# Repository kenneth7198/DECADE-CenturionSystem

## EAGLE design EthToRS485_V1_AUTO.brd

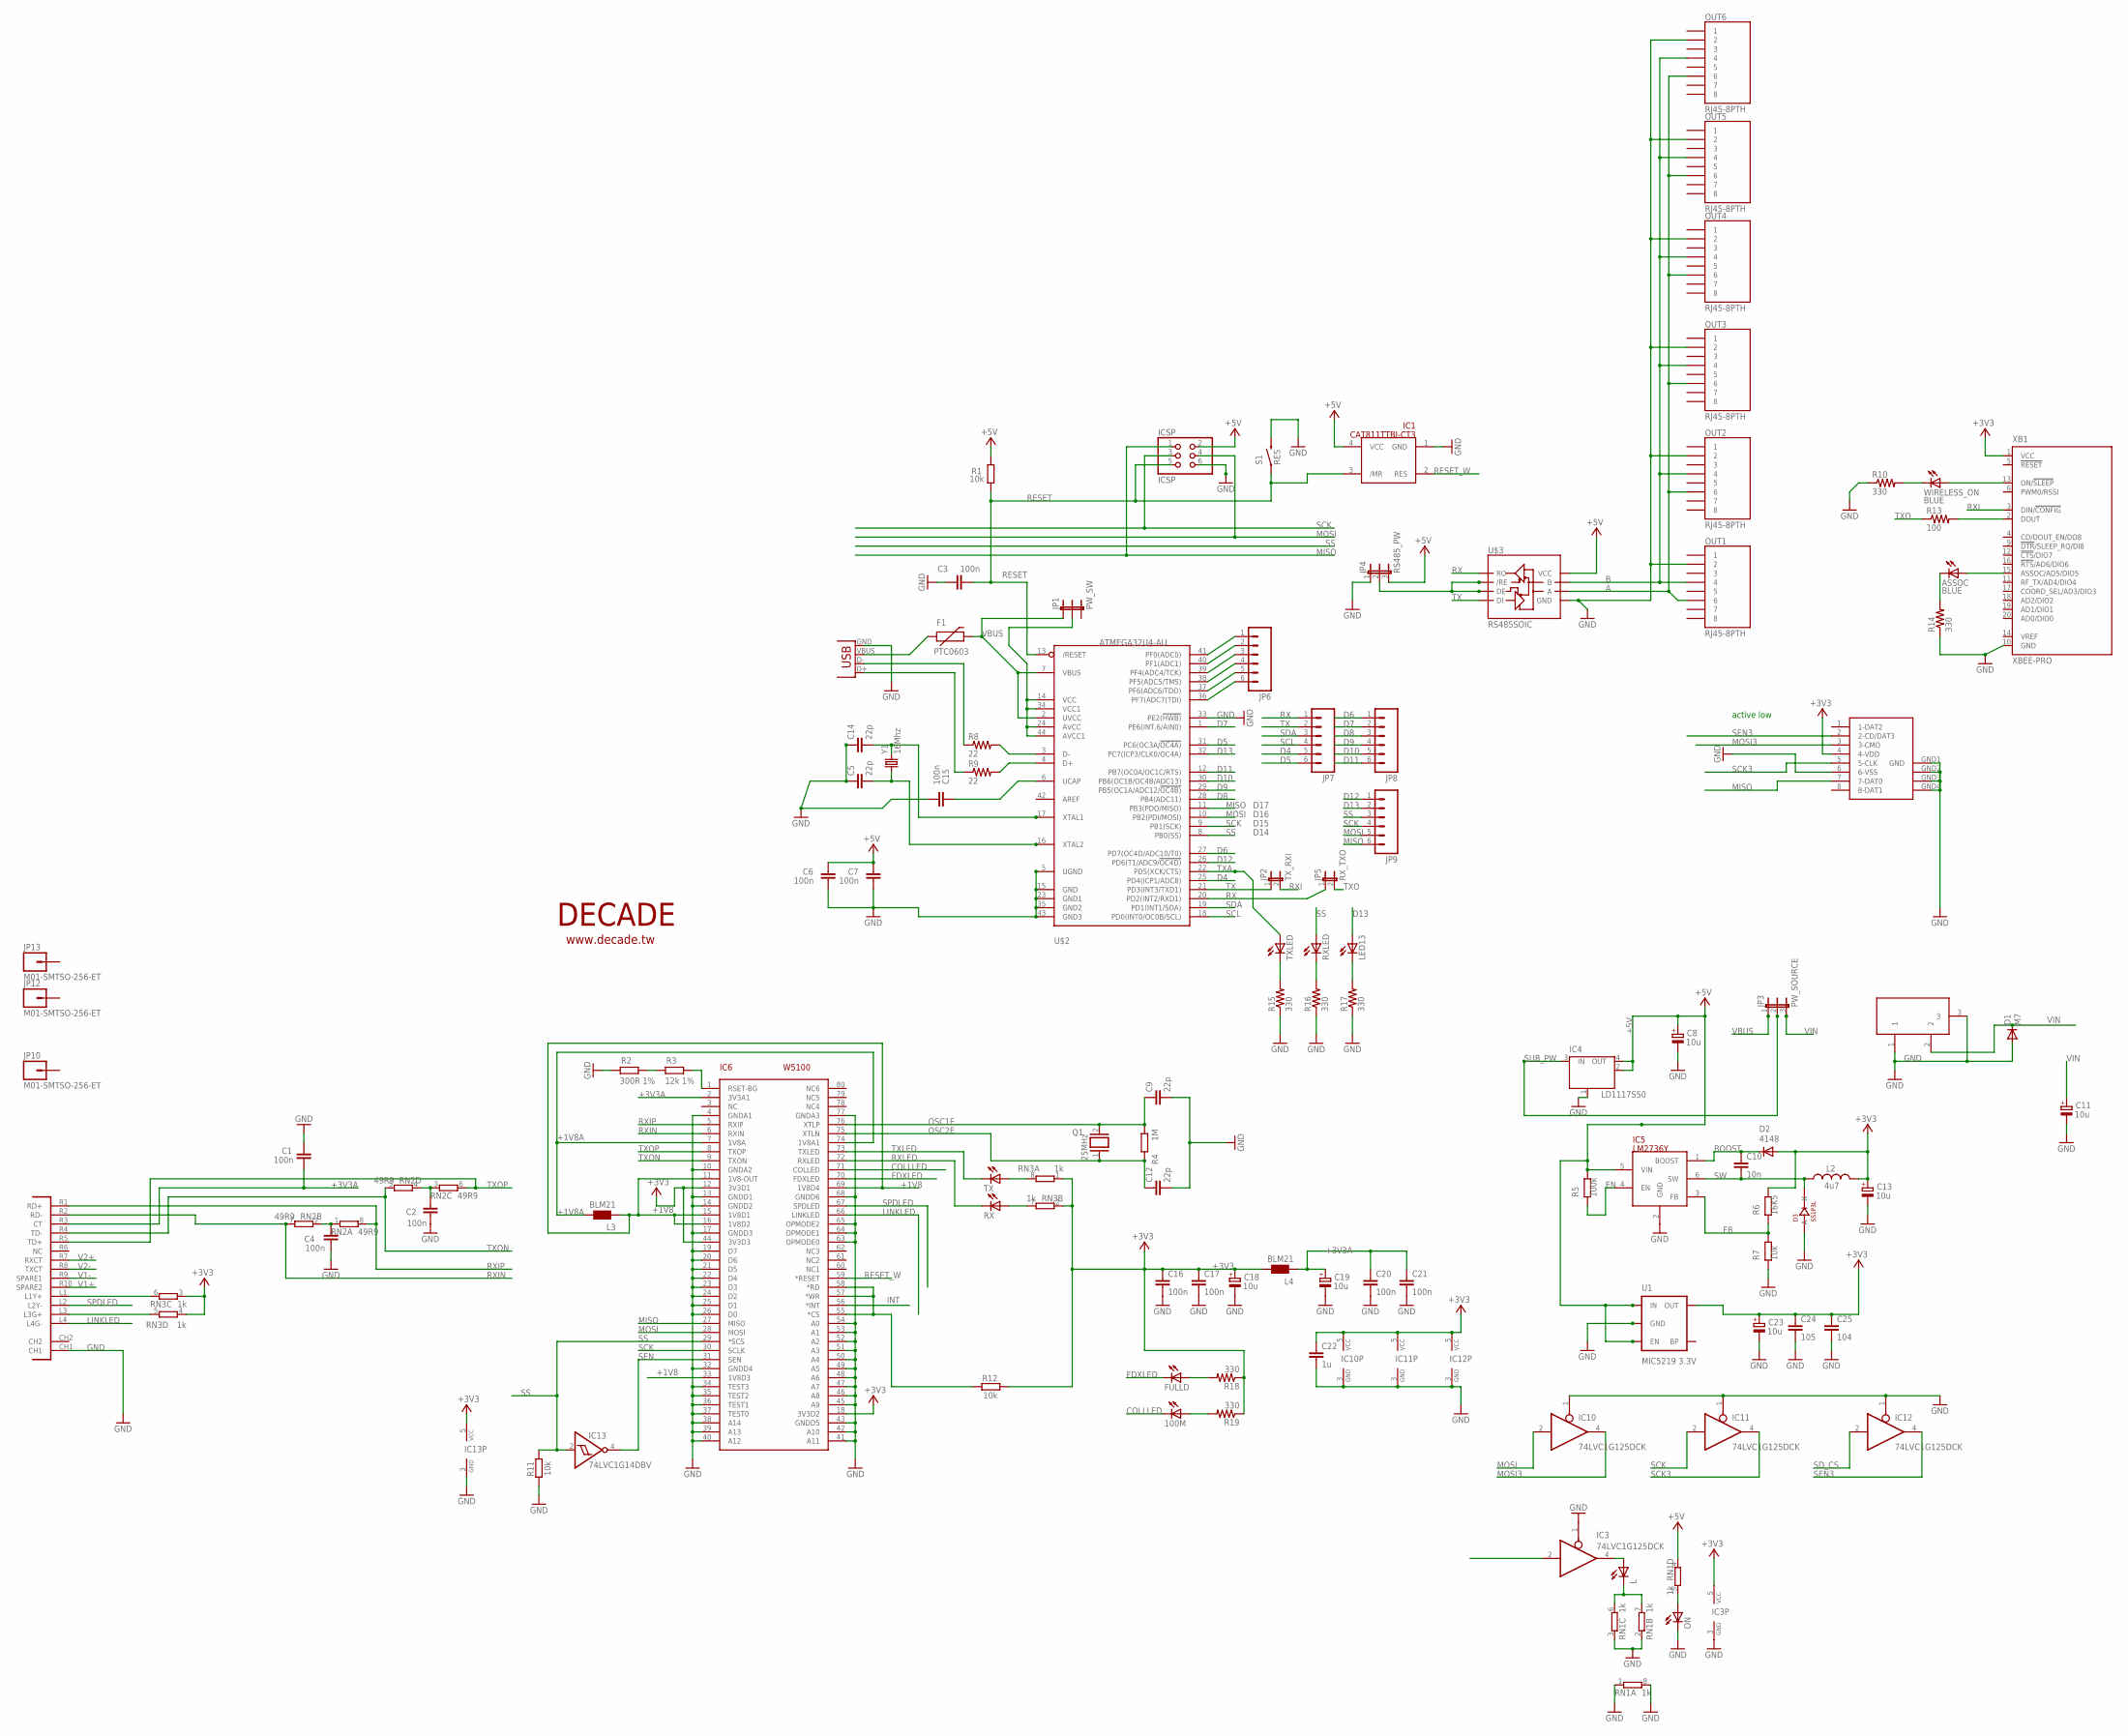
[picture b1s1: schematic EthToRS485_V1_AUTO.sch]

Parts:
100M: LEDCHIPLED_0805; CHIPLED_0805
ASSOC: BLUE; CHIPLED_0805
C1, C2, C3, C4, C6, C7, C15, C16, C17, C20, C21: 100n; C0603-ROUND
C5, C14: 22p; 0805
C8, C11, C13, C18, C19, C23: 10u; SMC_B
C9, C12: 22p; C0603-ROUND
C10: 10n; C0603-ROUND
C22: 1u; C0603-ROUND
C24: 105; C0603-ROUND
C25: 104; C0603-ROUND
D1: M7; SMB
D2: 4148; MINIMELF
D3: SS1P3L; DO220AAL
F1: PTC0603; 0603
FULLD: LEDCHIPLED_0805; CHIPLED_0805
IC1: CAT811TTBI-CT3; SOT143
IC3, IC10, IC11, IC12: 74LVC1G125DCK; SC70-5
IC4: LD1117S50; SOT223
IC5: LM2736Y; SOT23-6
IC6: W5100; SQFP-S-10X10-80
IC13: 74LVC1G14DBV; SOT23-5
ICSP: ICSP; 2X03
JP1: PW_SW; SJ_3
JP2: TX_RXI; JP1
JP3: PW_SOURCE; JP2
JP4: RS485_PW; JP2
JP5: RX_TXO; JP1
JP6, JP7, JP8, JP9: M06SIP; 1X06
JP10, JP12, JP13: M01-SMTSO-256-ET; SMTSO-256-ET
L: LEDCHIPLED_0805; CHIPLED_0805
L2: 4u7; SRR0604
L3, L4: BLM21; 0805
LED13: LEDCHIPLED_0805; CHIPLED_0805
ON: LEDCHIPLED_0805; CHIPLED_0805
OUT1, OUT2, OUT3, OUT4, OUT5, OUT6: RJ45-8PTH; RJ45-8
Q1: 25MHz; QS
R1, R7, R11, R12: 10k; R0603-ROUND
R2: 300R 1%; R0603-ROUND
R3: 12k 1%; R0603-ROUND
R4: 1M; R0603-ROUND
R5: 100k; R0603-ROUND
R6: 16K5; R0603-ROUND
R8, R9: 22; 0805
R10, R14, R15, R16, R17, R18, R19: 330; 0805
R13: 100; 0805
RN1, RN3: 1k; CAY16
RN2: 49R9; CAY16
RX: LEDCHIPLED_0805; CHIPLED_0805
RXLED: LEDCHIPLED_0805; CHIPLED_0805
S1: RES; TACTILE-SWITCH-1101NE
TX: LEDCHIPLED_0805; CHIPLED_0805
TXLED: LEDCHIPLED_0805; CHIPLED_0805
U1: MIC5219 3.3V; SOT23-5
U$1: POE-RJ45
U$2: ATMEGA32U4-AU; TQFP44
U$3: RS485SOIC; SO08
U$4: DECADE-LOGO-SMALL
WIRELESS_ON: BLUE; CHIPLED_0805
X1: DC21MMX; DC-21MM
X2: SDCARD-15TW-8821
X3: USBOLD; USB-MINIB-OLD
XB1: XBEE-PRO
Y1: 16Mhz; CRYSTAL-SMD-5X3

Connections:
+1V8: IC6.11 (1V8-OUT), IC6.15 (1V8D1), IC6.16 (1V8D2), IC6.33 (1V8D3), IC6.69 (1V8D4), L3.1
+1V8A: IC6.7 (1V8A), IC6.74 (1V8A1), L3.2
+3V3: C13.+, C16.1, C17.1, C18.+, C22.1, C23.+, C24.1, C25.1, D2.A, IC3.5 (VCC), IC6.12 (3V3D1), IC6.18 (3V3D2), IC6.44 (3V3D3), IC10.5 (VCC), IC11.5 (VCC), IC12.5 (VCC), IC13.5 (VCC), L2.P$2 (2), L4.2, R6.1, R12.2, R18.1, R19.1, RN3.1, RN3.2 (1), RN3.3 (1), RN3.4 (1), U1.5 (OUT), X2.4 (4-VDD), XB1.1 (VCC)
+3V3A: C1.1, C19.+, C20.1, C21.1, IC6.2 (3V3A1), L4.1, U$1.R3 (CT)
+5V: C6.1, C7.1, C8.+, IC1.4 (VCC), IC4.2 (OUT), IC4.4 (OUT), IC5.5 (VIN), ICSP.2, JP4.3, R1.2, R5.1, RN1.4 (1), U1.1 (IN), U1.3 (EN), U$3.8 (VCC)
A: OUT1.6, OUT2.6, OUT3.6, OUT4.6, OUT5.6, OUT6.6, U$3.6 (A)
AD0: JP6.1, U$2.41 (PF0(ADC0))
AD1: JP6.2, U$2.40 (PF1(ADC1))
AD2: JP6.3, U$2.39 (PF4(ADC4/TCK))
AD3: JP6.4, U$2.38 (PF5(ADC5/TMS))
AD4: JP6.5, U$2.37 (PF6(ADC6/TDO))
AD5: JP6.6, U$2.36 (PF7(ADC7(TDI))
B: OUT1.4, OUT2.4, OUT3.4, OUT4.4, OUT5.4, OUT6.4, U$3.7 (B)
BOOST: C10.1, D2.C, IC5.1 (BOOST)
COLLLED: 100M.C, IC6.71 (COLLED)
D4: JP7.5, U$2.25 (PD4(ICP1/ADC8))
D5: JP7.6, U$2.31 (PC6(OC3A/!OC4A))
D6: JP8.1, U$2.27 (PD7(OC4D/ADC10/T0))
D7: JP8.2, U$2.1 (PE6(INT.6/AIN0))
D8: JP8.3, U$2.28 (PB4(ADC11))
D9: JP8.4, U$2.29 (PB5(OC1A/ADC12/!OC4B))
D10: JP8.5, U$2.30 (PB6(OC1B/OC4B/ADC13))
D11: JP8.6, U$2.12 (PB7(OC0A/OC1C/RTS))
D12: JP9.1, U$2.26 (PD6(T1/ADC9/!OC4D))
D13: JP9.2, LED13.A, U$2.32 (PC7(ICP3/CLK0/OC4A))
EN: IC5.4 (EN), R5.2
FB: IC5.3 (FB), R6.2, R7.1
FDXLED: FULLD.C, IC6.70 (FDXLED)
GND: C1.2, C2.1, C3.2, C4.1, C5.1, C6.2, C7.2, C8.-, C9.2, C11.-, C12.2, C13.-, C14.1, C15.2, C16.2, C17.2, C18.-, C19.-, C20.2, C21.2, C22.2, C23.-, C24.2, C25.2, D1.A, D3.P$2 (A), IC1.1 (GND), IC3.1 (OE), IC3.3 (GND), IC4.1 (GND/ADJ), IC5.2 (GND), IC6.4 (GNDA1), IC6.10 (GNDA2), IC6.13 (GNDD1), IC6.14 (GNDD2), IC6.17 (GNDD3), IC6.19 (D7), IC6.20 (D6), IC6.21 (D5), IC6.22 (D4), IC6.23 (D3), IC6.24 (D2), IC6.25 (D1), IC6.26 (D0), IC6.32 (GNDD4), IC6.34 (TEST3), IC6.35 (TEST2), IC6.36 (TEST1), IC6.37 (TEST0), IC6.38 (A14), IC6.39 (A13), IC6.40 (A12), IC6.41 (A11), IC6.42 (A10), IC6.43 (GNDD5), IC6.45 (A9), IC6.46 (A8), IC6.47 (A7), IC6.48 (A6), IC6.49 (A5), IC6.50 (A4), IC6.51 (A3), IC6.52 (A2), IC6.53 (A1), IC6.54 (A0), IC6.63 (OPMODE0), IC6.64 (OPMODE1), IC6.65 (OPMODE2), IC6.68 (GNDD6), IC6.77 (GNDA3), IC10.1 (OE), IC10.3 (GND), IC11.1 (OE), IC11.3 (GND), IC12.1 (OE), IC12.3 (GND), IC13.3 (GND), ICSP.6, JP4.1, ON.C, OUT1.2, OUT2.2, OUT3.2, OUT4.2, OUT5.2, OUT6.2, R2.2, R7.2, R10.1, R11.1, R14.1, R15.1, R16.1, R17.1, RN1.1, RN1.2 (1), RN1.3 (1), RN1.8 (2), S1.P$2 (2), U1.2 (GND), U$1.CH1, U$2.5 (UGND), U$2.15 (GND), U$2.23 (GND1), U$2.33 (PE2(!HWB)), U$2.35 (GND2), U$2.43 (GND3), U$3.5 (GND), X1.1, X1.3, X2.6 (6-VSS), X2.GND1 (GND), X2.GND2 (GND1), X2.GND3 (GND2), X2.GND4 (GND3), X3.GND, XB1.10 (GND)
INT: IC6.56 (*INT)
LINKLED: IC6.66 (LINKLED), U$1.L4 (L4G-)
MISO: IC6.27 (MISO), ICSP.1, JP9.6, U$2.11 (PB3(PDO/MISO)), X2.7 (7-DAT0)
MOSI: IC6.28 (MOSI), IC10.2 (I), ICSP.4, JP9.5, U$2.10 (PB2(PDI/MOSI))
MOSI3: IC10.4 (O), X2.3 (3-CMO)
unnamed: IC3.4 (O), L.A
unnamed: RN3.5 (2), U$1.L3 (L3G+)
unnamed: RN3.6 (2), U$1.L1 (L1Y+)
unnamed: L.C, RN1.6 (2), RN1.7 (2)
unnamed: C5.2, U$2.16 (XTAL2), Y1.1
unnamed: C14.2, U$2.17 (XTAL1), Y1.3 (2)
unnamed: ON.A, RN1.5 (2)
unnamed: RN3.8 (2), TX.A
unnamed: C2.2, RN2.3 (1), RN2.4 (1)
unnamed: R8.2, U$2.3 (D-)
unnamed: R9.2, U$2.4 (D+)
unnamed: R8.1, X3.D-
unnamed: R9.1, X3.D+
unnamed: F1.1, X3.VBUS
unnamed: R15.2, TXLED.C
unnamed: R13.2, XB1.2 (DOUT)
unnamed: C15.1, U$2.6 (UCAP)
unnamed: JP1.2, U$2.14 (VCC), U$2.24 (AVCC), U$2.34 (VCC1), U$2.44 (AVCC1)
unnamed: R10.2, WIRELESS_ON.C
unnamed: JP4.2, U$3.2 (/RE), U$3.3 (DE)
unnamed: RN3.7 (2), RX.A
unnamed: WIRELESS_ON.A, XB1.13 (ON/!SLEEP)
unnamed: ASSOC.A, XB1.15 (ASSOC/AD5/DIO5)
unnamed: ASSOC.C, R14.2
unnamed: FULLD.A, R18.2
unnamed: C4.2, RN2.1, RN2.2 (1)
unnamed: R2.1, R3.2
unnamed: IC6.1 (RSET-BG), R3.1
unnamed: IC6.55 (*CS), IC6.57 (*WR), IC6.58 (*RD), R12.1
unnamed: R16.2, RXLED.C
unnamed: LED13.C, R17.2
unnamed: 100M.A, R19.2
OSC1E: C9.1, IC6.76 (XTLP), Q1.2, R4.1
OSC2E: C12.1, IC6.75 (XTLN), Q1.1, R4.2
RESET: C3.1, IC1.3 (/MR), ICSP.5, R1.1, S1.P$1 (1), U$2.13 (/RESET)
RESET_W: IC1.2 (RES), IC6.59 (*RESET)
RX: JP5.1, JP7.1, U$2.20 (PD2(INT2/RXD1)), U$3.1 (RO)
RXI: JP2.2, XB1.3 (DIN/!CONFIG)
RXIN: IC6.6 (RXIN), RN2.7 (2), U$1.R2 (RD-)
RXIP: IC6.5 (RXIP), RN2.8 (2), U$1.R1 (RD+)
RXLED: IC6.72 (RXLED), RX.C
SCK: IC6.30 (SCLK), IC11.2 (I), ICSP.3, JP9.4, U$2.9 (PB1(SCK))
SCK3: IC11.4 (O), X2.5 (5-CLK)
SCL: JP7.4, U$2.18 (PD0(INT0/OC0B/SCL))
SDA: JP7.3, U$2.19 (PD1(INT1/SDA))
SD_CS: IC12.2 (I)
SEN: IC6.31 (SEN), IC13.4 (O)
SEN3: IC12.4 (O), X2.2 (2-CD/DAT3)
SPDLED: IC6.67 (SPDLED), U$1.L2 (L2Y-)
SS: IC6.29 (*SCS), IC13.2 (I), JP9.3, R11.2, RXLED.A, U$2.8 (PB0(SS))
SUB_PW: IC4.3 (IN), JP3.2
SW: C10.2, D3.P$1 (K), IC5.6 (SW), L2.P$1 (1)
TX: JP2.1, JP7.2, U$2.21 (PD3(INT3/TXD1)), U$3.4 (DI)
TXA: TXLED.A, U$2.22 (PD5(XCK/CTS))
TXLED: IC6.73 (TXLED), TX.C
TXO: JP5.2, R13.1
TXON: IC6.9 (TXON), RN2.5 (2), U$1.R4 (TD-)
TXOP: IC6.8 (TXOP), RN2.6 (2), U$1.R5 (TD+)
V1+: U$1.R10 (SPARE2)
V1-: U$1.R9 (SPARE1)
V2+: U$1.R7 (RXCT)
V2-: U$1.R8 (TXCT)
VBUS: F1.2, JP1.1, JP3.1, U$2.2 (UVCC), U$2.7 (VBUS)
VIN: C11.+, D1.C, JP3.3, X1.2

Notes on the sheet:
active low
D15
D14
D16
D17

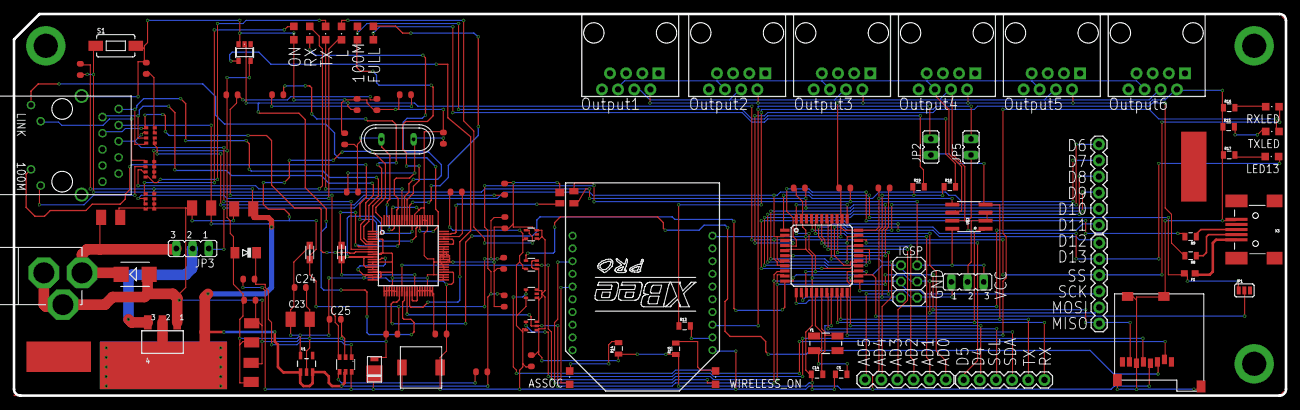
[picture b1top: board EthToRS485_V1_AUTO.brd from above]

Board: 2 copper layers, 200.0 x 60.0 mm, 105 parts (0 on the bottom side), 92 nets.

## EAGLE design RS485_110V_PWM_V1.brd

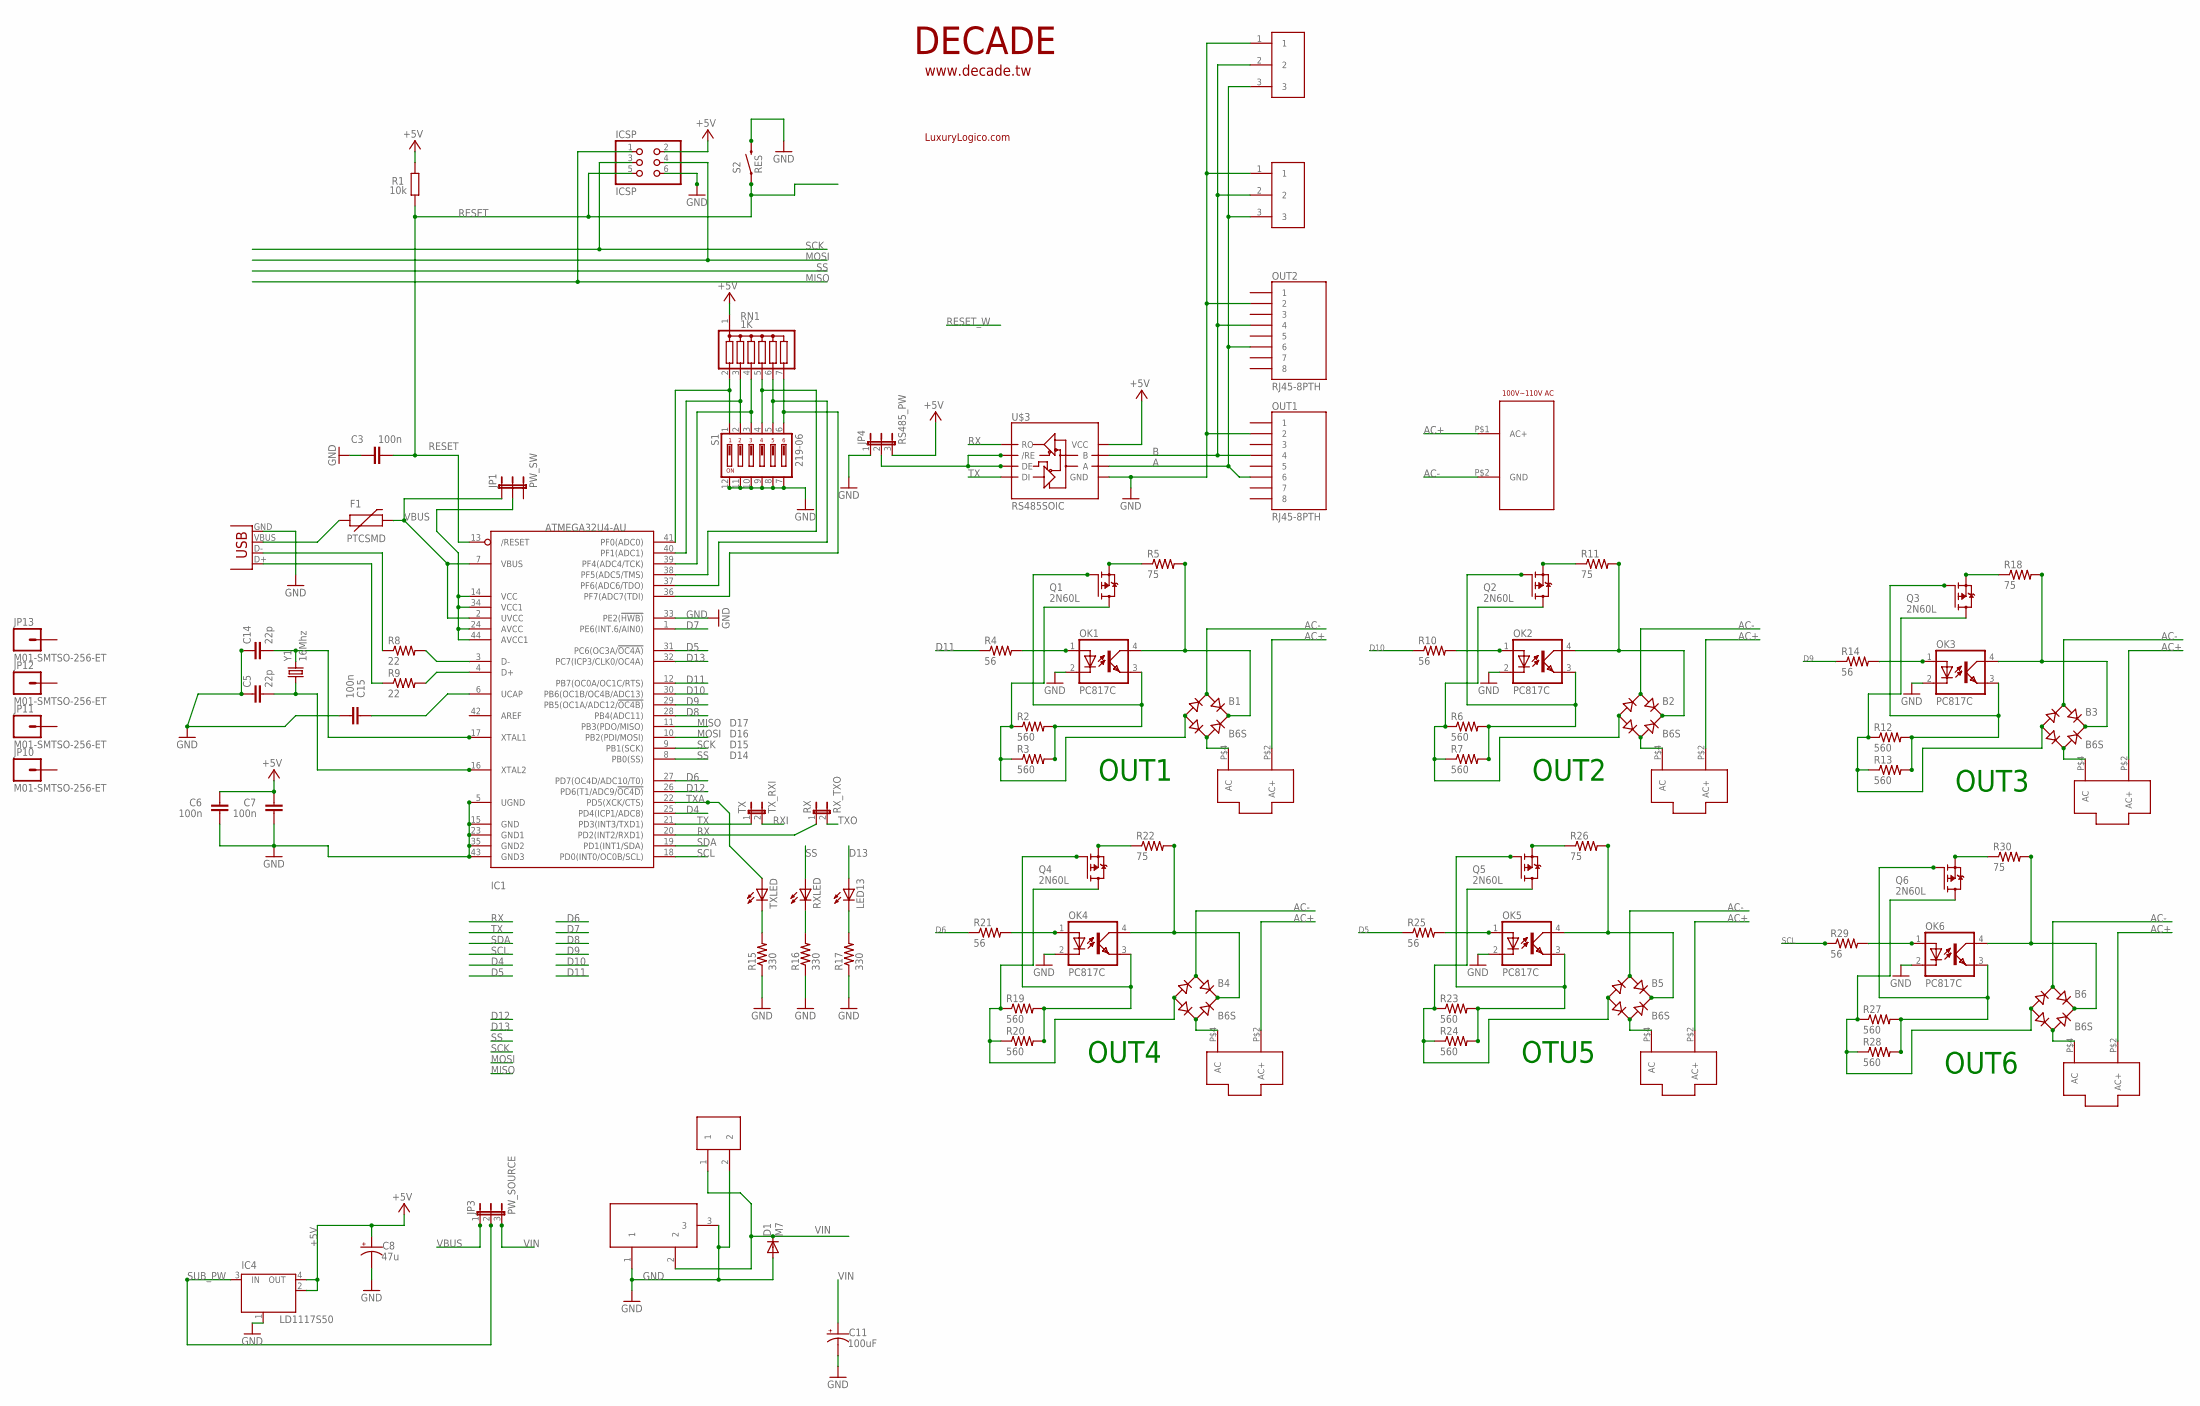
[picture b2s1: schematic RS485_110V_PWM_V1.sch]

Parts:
B1, B2, B3, B4, B5, B6: B6S; MBS
C3, C6, C7, C15: 100n; C0603-ROUND
C5, C14: 22p; 0805
C8: 47u; PANASONIC_E
C11: 100uF; PANASONIC_E
D1: M7; SMB
F1: PTCSMD; PTC-1206
IC1: ATMEGA32U4-AU; TQFP44
IC4: LD1117S50; SOT223
ICSP: ICSP; 2X03
JP1: PW_SW; SJ_3
JP3: PW_SOURCE; JP2
JP4: RS485_PW; JP2
JP10, JP11, JP12, JP13: M01-SMTSO-256-ET; SMTSO-256-ET
LED13: LEDCHIPLED_0805; CHIPLED_0805
OK1, OK2, OK3, OK4, OK5, OK6: PC817C; DIP4-400
OUT1, OUT2: RJ45-8PTH; RJ45-8
Q1, Q2, Q3, Q4, Q5, Q6: 2N60L; TO252
R1: 10k; R0603-ROUND
R2, R3, R6, R7, R12, R13, R19, R20, R23, R24, R27, R28: 560; 1206
R4, R10, R14, R21, R25, R29: 56; 1206
R5, R11, R18, R22, R26, R30: 75; AXIAL-0.6
R8, R9: 22; 0805
R15, R16, R17: 330; 0805
RN1: 1K; SIL7
RX: RX_TXO; JP1
RXLED: LEDCHIPLED_0805; CHIPLED_0805
S1: 219-06; CTS-219-06
S2: RES; TACTILE-SWITCH-1101NE
TX: TX_RXI; JP1
TXLED: LEDCHIPLED_0805; CHIPLED_0805
U$1: DECADE-ACIN; DECADE-AC_IN
U$2, U$4, U$5, U$6, U$7, U$8: DECADE-ACPW; DECADE-ACPWR
U$3: RS485SOIC; SO08
U$9: DECADE-5MM-CONN; DECADE-5MM-CON-1X2
U$10, U$11: DECADE-5MM-CON-1X3
U$12: DECADE-LOGO-SMALL
U$13: LL-LUXURYLOGICO.COM; DECADE-LL-LOGO-SMALL
X1: DC21MMX; DC-21MM
X3: USBOLD; USB-MINIB-OLD
Y1: 16Mhz; CRYSTAL-SMD-5X3

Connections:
+5V: C6.1, C7.1, C8.+, IC4.2 (OUT), IC4.4 (OUT), ICSP.2, JP4.3, R1.2, RN1.1, U$3.8 (VCC)
A: OUT1.6, OUT2.6, U$3.6 (A), U$10.3, U$11.3
AC+: U$1.P$1 (AC+), U$2.P$2 (AC+), U$4.P$2 (AC+), U$5.P$2 (AC+), U$6.P$2 (AC+), U$7.P$2 (AC+), U$8.P$2 (AC+)
AC-: B1.AC1, B2.AC1, B3.AC1, B4.AC1, B5.AC1, B6.AC1, U$1.P$2 (GND)
B: OUT1.4, OUT2.4, U$3.7 (B), U$10.2, U$11.2
D4: IC1.25 (PD4(ICP1/ADC8))
D5: IC1.31 (PC6(OC3A/!OC4A)), R25.1
D6: IC1.27 (PD7(OC4D/ADC10/T0)), R21.1
D7: IC1.1 (PE6(INT.6/AIN0))
D8: IC1.28 (PB4(ADC11))
D9: IC1.29 (PB5(OC1A/ADC12/!OC4B)), R14.1
D10: IC1.30 (PB6(OC1B/OC4B/ADC13)), R10.1
D11: IC1.12 (PB7(OC0A/OC1C/RTS)), R4.1
D12: IC1.26 (PD6(T1/ADC9/!OC4D))
D13: IC1.32 (PC7(ICP3/CLK0/OC4A)), LED13.A
GND: C3.2, C5.1, C6.2, C7.2, C8.-, C11.-, C14.1, C15.2, D1.A, IC1.5 (UGND), IC1.15 (GND), IC1.23 (GND1), IC1.33 (PE2(!HWB)), IC1.35 (GND2), IC1.43 (GND3), IC4.1 (GND/ADJ), ICSP.6, JP4.1, OK1.2 (C), OK2.2 (C), OK3.2 (C), OK4.2 (C), OK5.2 (C), OK6.2 (C), OUT1.2, OUT2.2, R15.1, R16.1, R17.1, S1.7, S1.8, S1.9, S1.10, S1.11, S1.12, S2.P$2 (2), U$3.5 (GND), U$9.2, U$10.1, U$11.1, X1.1, X1.3, X3.GND
MISO: IC1.11 (PB3(PDO/MISO)), ICSP.1
MOSI: IC1.10 (PB2(PDI/MOSI)), ICSP.4
unnamed: OK1.1 (A), R4.2
unnamed: Q1.2 (S), R5.P$1 (1)
unnamed: OK1.3 (EMIT), Q1.1 (G), R2.2, R3.2
unnamed: OK2.1 (A), R10.2
unnamed: Q2.2 (S), R11.P$1 (1)
unnamed: C5.2, IC1.16 (XTAL2), Y1.1
unnamed: C14.2, IC1.17 (XTAL1), Y1.3 (2)
unnamed: B1.-, Q1.3 (D), R2.1, R3.1
unnamed: OK2.3 (EMIT), Q2.1 (G), R6.2, R7.2
unnamed: B1.AC2, U$2.P$4 (AC)
unnamed: IC1.3 (D-), R8.2
unnamed: IC1.4 (D+), R9.2
unnamed: R8.1, X3.D-
unnamed: R9.1, X3.D+
unnamed: F1.1, X3.VBUS
unnamed: R15.2, TXLED.C
unnamed: B2.-, Q2.3 (D), R6.1, R7.1
unnamed: C15.1, IC1.6 (UCAP)
unnamed: IC1.14 (VCC), IC1.24 (AVCC), IC1.34 (VCC1), IC1.44 (AVCC1), JP1.2
unnamed: B1.+, OK1.4 (COL), R5.P$2 (2)
unnamed: JP4.2, U$3.2 (/RE), U$3.3 (DE)
unnamed: B2.AC2, U$4.P$4 (AC)
unnamed: B2.+, OK2.4 (COL), R11.P$2 (2)
unnamed: OK3.1 (A), R14.2
unnamed: Q3.2 (S), R18.P$1 (1)
unnamed: OK3.3 (EMIT), Q3.1 (G), R12.2, R13.2
unnamed: B3.-, Q3.3 (D), R12.1, R13.1
unnamed: B3.AC2, U$5.P$4 (AC)
unnamed: B3.+, OK3.4 (COL), R18.P$2 (2)
unnamed: OK4.1 (A), R21.2
unnamed: Q4.2 (S), R22.P$1 (1)
unnamed: OK4.3 (EMIT), Q4.1 (G), R19.2, R20.2
unnamed: B4.-, Q4.3 (D), R19.1, R20.1
unnamed: B4.AC2, U$6.P$4 (AC)
unnamed: B4.+, OK4.4 (COL), R22.P$2 (2)
unnamed: OK5.1 (A), R25.2
unnamed: R16.2, RXLED.C
unnamed: LED13.C, R17.2
unnamed: Q5.2 (S), R26.P$1 (1)
unnamed: IC1.41 (PF0(ADC0)), RN1.2, S1.1
unnamed: IC1.40 (PF1(ADC1)), RN1.3, S1.2
unnamed: IC1.39 (PF4(ADC4/TCK)), RN1.4, S1.3
unnamed: IC1.38 (PF5(ADC5/TMS)), RN1.5, S1.4
unnamed: IC1.37 (PF6(ADC6/TDO)), RN1.6, S1.5
unnamed: IC1.36 (PF7(ADC7(TDI)), RN1.7, S1.6
unnamed: OK5.3 (EMIT), Q5.1 (G), R23.2, R24.2
unnamed: B5.-, Q5.3 (D), R23.1, R24.1
unnamed: B5.AC2, U$7.P$4 (AC)
unnamed: B5.+, OK5.4 (COL), R26.P$2 (2)
unnamed: OK6.1 (A), R29.2
unnamed: Q6.2 (S), R30.P$1 (1)
unnamed: OK6.3 (EMIT), Q6.1 (G), R27.2, R28.2
unnamed: B6.-, Q6.3 (D), R27.1, R28.1
unnamed: B6.AC2, U$8.P$4 (AC)
unnamed: B6.+, OK6.4 (COL), R30.P$2 (2)
RESET: C3.1, IC1.13 (/RESET), ICSP.5, R1.1, S2.P$1 (1)
RX: IC1.20 (PD2(INT2/RXD1)), RX.1, U$3.1 (RO)
RXI: TX.2
SCK: IC1.9 (PB1(SCK)), ICSP.3
SCL: IC1.18 (PD0(INT0/OC0B/SCL)), R29.1
SDA: IC1.19 (PD1(INT1/SDA))
SS: IC1.8 (PB0(SS)), RXLED.A
SUB_PW: IC4.3 (IN), JP3.2
TX: IC1.21 (PD3(INT3/TXD1)), TX.1, U$3.4 (DI)
TXA: IC1.22 (PD5(XCK/CTS)), TXLED.A
TXO: RX.2
VBUS: F1.2, IC1.2 (UVCC), IC1.7 (VBUS), JP1.1, JP3.1
VIN: C11.+, D1.C, JP3.3, U$9.1, X1.2

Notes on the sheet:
D15
D14
D16
D17
OUT1
OUT2
OUT3
OUT4
OTU5
OUT6

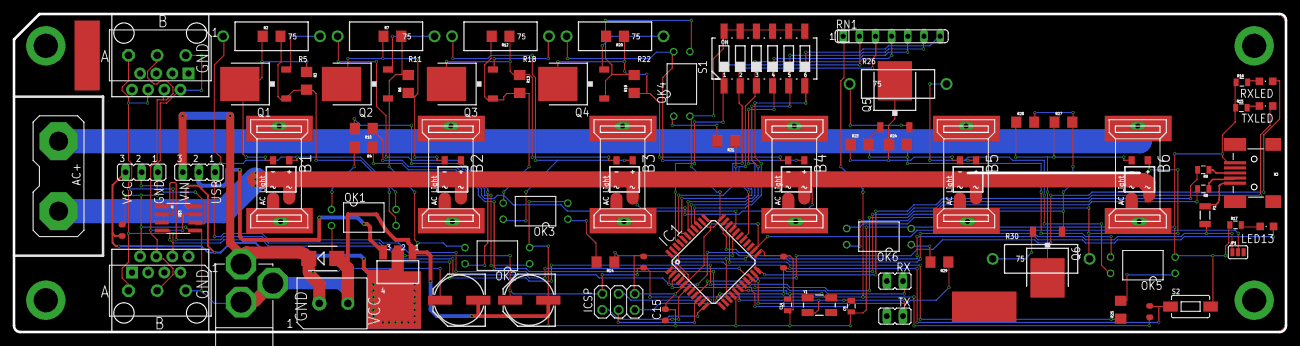
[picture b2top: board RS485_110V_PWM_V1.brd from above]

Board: 2 copper layers, 200.0 x 50.0 mm, 94 parts (0 on the bottom side), 79 nets.

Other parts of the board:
E$1: DECADE-LL-LOGO-SMALL

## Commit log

2013-01-07 new upload

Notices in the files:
parts and their libraries:
SparkFun-FreqCtrl: Licensing: CC v3.0 Share-Alike You are welcome to use this library for commercial purposes.
